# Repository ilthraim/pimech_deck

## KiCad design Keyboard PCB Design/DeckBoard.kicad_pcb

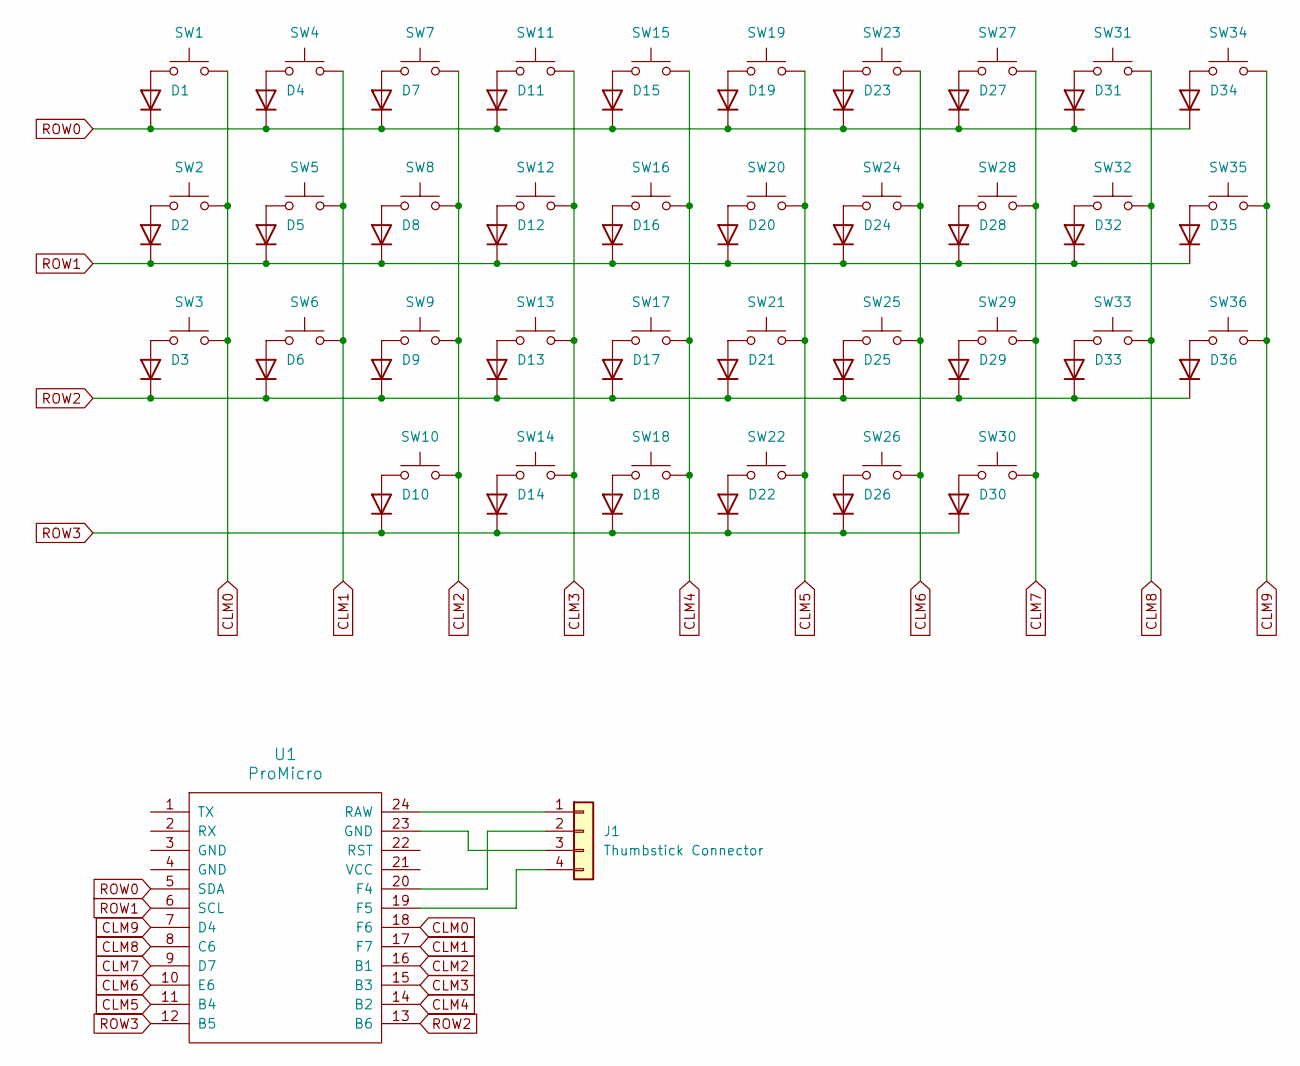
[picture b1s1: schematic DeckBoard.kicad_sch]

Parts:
D1, D2, D3, D4, D5, D6, D7, D8, D9, D10, D11, D12, D13, D14, D15, D16, D17, D18, D19, D20, D21, D22, D23, D24, D25, D26, D27, D28, D29, D30, D31, D32, D33, D34, D35, D36: D; D_0805_2012Metric
J1: Thumbstick Connector; PinHeader_1x04_P2.54mm_Vertical
SW1, SW2, SW3, SW4, SW5, SW6, SW7, SW8, SW9, SW10, SW11, SW12, SW13, SW14, SW15, SW16, SW17, SW18, SW19, SW20, SW21, SW22, SW23, SW24, SW25, SW26, SW27, SW28, SW29, SW30, SW31, SW32, SW33, SW34, SW35, SW36: SW_Push; SW_PG1350
U1: ProMicro

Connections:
CLM0: SW1.2, SW2.2, SW3.2, U1.18 (F6)
CLM1: SW4.2, SW5.2, SW6.2, U1.17 (F7)
CLM2: SW7.2, SW8.2, SW9.2, SW10.2, U1.16 (B1)
CLM3: SW11.2, SW12.2, SW13.2, SW14.2, U1.15 (B3)
CLM4: SW15.2, SW16.2, SW17.2, SW18.2, U1.14 (B2)
CLM5: SW19.2, SW20.2, SW21.2, SW22.2, U1.11 (B4)
CLM6: SW23.2, SW24.2, SW25.2, SW26.2, U1.10 (E6)
CLM7: SW27.2, SW28.2, SW29.2, SW30.2, U1.9 (D7)
CLM8: SW31.2, SW32.2, SW33.2, U1.8 (C6)
CLM9: SW34.2, SW35.2, SW36.2, U1.7 (D4)
unnamed: D1.2 (A), SW1.1
unnamed: D2.2 (A), SW2.1
unnamed: D3.2 (A), SW3.1
unnamed: D4.2 (A), SW4.1
unnamed: D5.2 (A), SW5.1
unnamed: D6.2 (A), SW6.1
unnamed: D7.2 (A), SW7.1
unnamed: D8.2 (A), SW8.1
unnamed: D9.2 (A), SW9.1
unnamed: D10.2 (A), SW10.1
unnamed: D11.2 (A), SW11.1
unnamed: D12.2 (A), SW12.1
unnamed: D13.2 (A), SW13.1
unnamed: D14.2 (A), SW14.1
unnamed: D15.2 (A), SW15.1
unnamed: D16.2 (A), SW16.1
unnamed: D17.2 (A), SW17.1
unnamed: D18.2 (A), SW18.1
unnamed: D19.2 (A), SW19.1
unnamed: D20.2 (A), SW20.1
unnamed: D21.2 (A), SW21.1
unnamed: D22.2 (A), SW22.1
unnamed: D23.2 (A), SW23.1
unnamed: D24.2 (A), SW24.1
unnamed: D25.2 (A), SW25.1
unnamed: D26.2 (A), SW26.1
unnamed: D27.2 (A), SW27.1
unnamed: D28.2 (A), SW28.1
unnamed: D29.2 (A), SW29.1
unnamed: D30.2 (A), SW30.1
unnamed: D31.2 (A), SW31.1
unnamed: D32.2 (A), SW32.1
unnamed: D33.2 (A), SW33.1
unnamed: D34.2 (A), SW34.1
unnamed: D35.2 (A), SW35.1
unnamed: D36.2 (A), SW36.1
unnamed: J1.1, U1.24 (RAW)
unnamed: J1.2, U1.20 (F4)
unnamed: J1.3, U1.23 (GND)
unnamed: J1.4, U1.19 (F5)
ROW0: D1.1 (K), D4.1 (K), D7.1 (K), D11.1 (K), D15.1 (K), D19.1 (K), D23.1 (K), D27.1 (K), D31.1 (K), D34.1 (K), U1.5 (SDA)
ROW1: D2.1 (K), D5.1 (K), D8.1 (K), D12.1 (K), D16.1 (K), D20.1 (K), D24.1 (K), D28.1 (K), D32.1 (K), D35.1 (K), U1.6 (SCL)
ROW2: D3.1 (K), D6.1 (K), D9.1 (K), D13.1 (K), D17.1 (K), D21.1 (K), D25.1 (K), D29.1 (K), D33.1 (K), D36.1 (K), U1.13 (B6)
ROW3: D10.1 (K), D14.1 (K), D18.1 (K), D22.1 (K), D26.1 (K), D30.1 (K), U1.12 (B5)

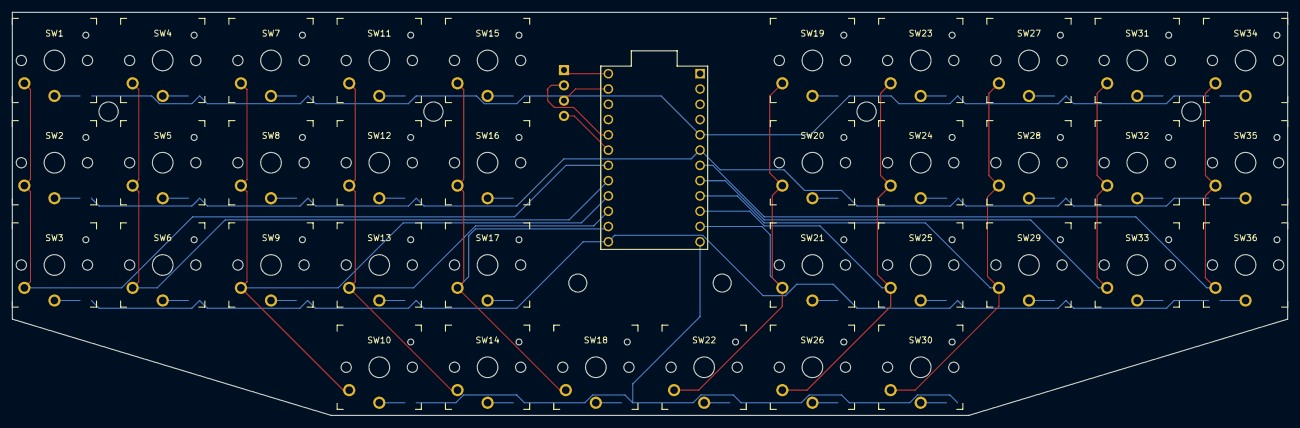
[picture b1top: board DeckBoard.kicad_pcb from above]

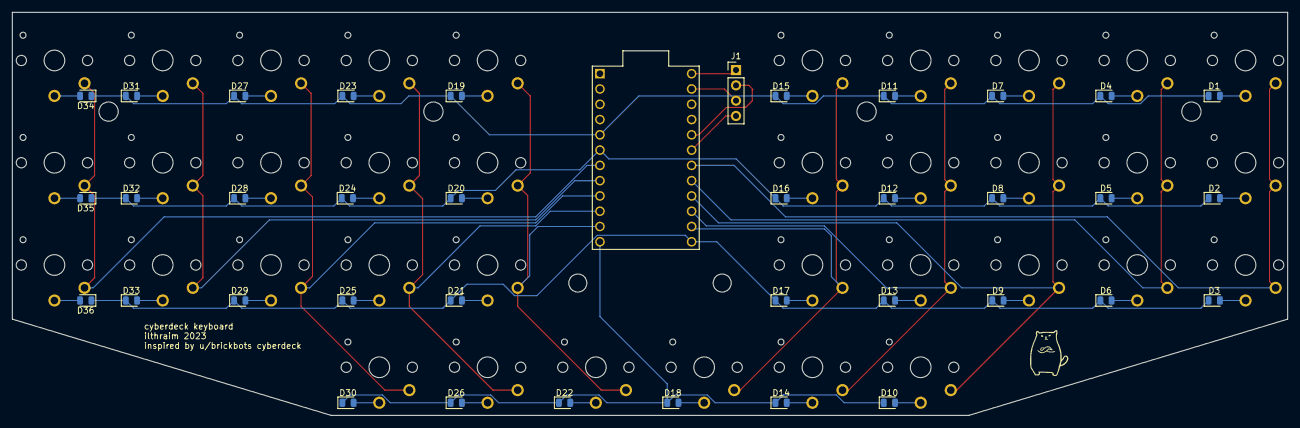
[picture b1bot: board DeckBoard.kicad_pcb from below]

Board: 2 copper layers, 212.0 x 67.0 mm, 74 parts (38 on the bottom side), 54 nets.

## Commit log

2023-09-10 Added Kicad design files for added keyboard PCB
2023-09-10 renamed pcb folder
2023-09-11 Fixed trace intersecting pad and moved joystick closer
2023-11-20 Heightened enclosure for PCB addition
2023-11-27 Updated stls
